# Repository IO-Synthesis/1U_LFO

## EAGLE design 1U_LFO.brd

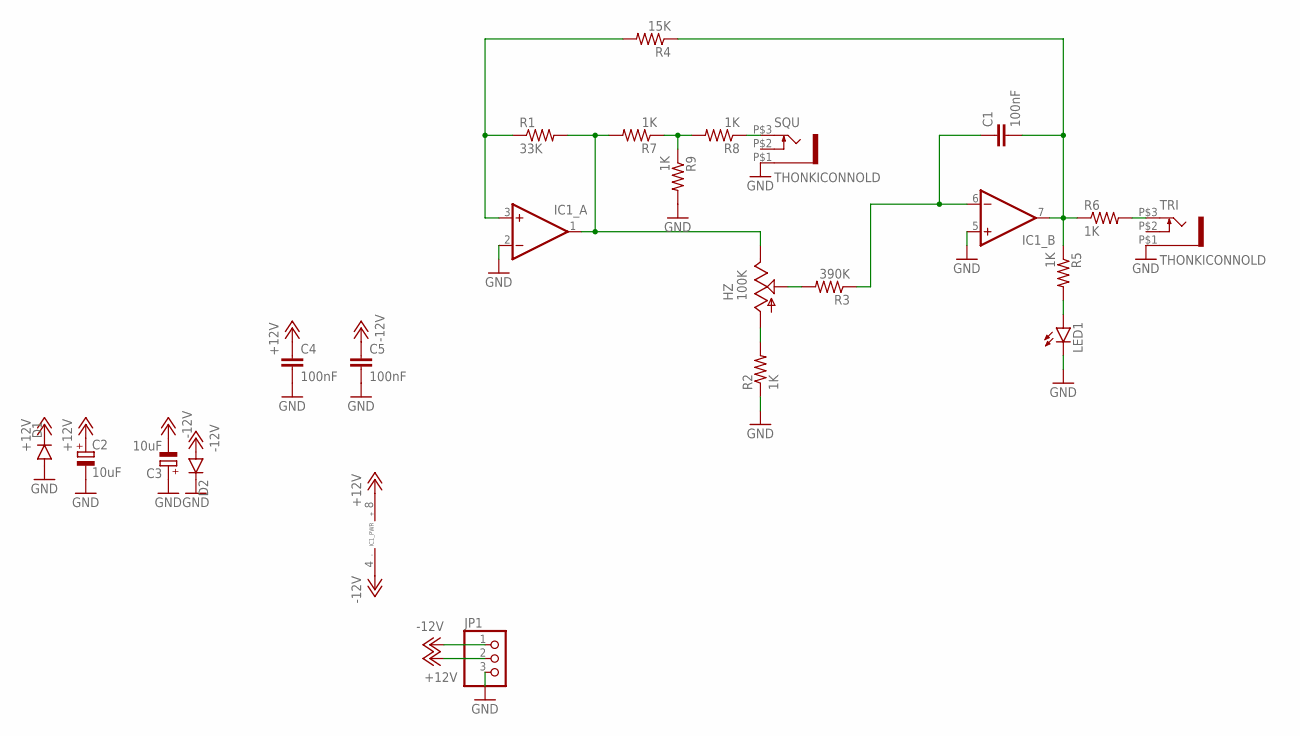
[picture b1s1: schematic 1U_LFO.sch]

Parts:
C1, C4, C5: 100nF; 0603-CAP
C2, C3: 10uF; CASE_B
D1, D2: DIODESOD123; SOD-123
HZ: 100K; 9MM_SNAP-IN_POT
IC1: DUALSMD; SO08
JP1: EUROPWR_TILE-TILE; 1X03_EUROPWR_TILE
LED1: LED3MM
R1: 33K; 0603-RES
R2, R5, R6, R7, R8, R9: 1K; 0603-RES
R3: 390K; 0603-RES
R4: 15K; 0603-RES
SQU: THONKICONNOLD; THONKICONN
TRI: THONKICONNOLD; THONKICONN

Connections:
+12V: C2.+, C4.1, D1.C, IC1.8 (V+), JP1.2
-12V: C3.-, C5.1, D2.A, IC1.4 (V-), JP1.1
GND: C2.-, C3.+, C4.2, C5.2, D1.A, D2.C, IC1.2 (-IN), IC1.5 (+IN), JP1.3, LED1.K (C), R2.1, R9.2, SQU.P$1 (5), TRI.P$1 (5)
unnamed: HZ.3 (E), IC1.1 (OUT), R1.2, R7.2
unnamed: HZ.1 (A), R2.2
unnamed: HZ.2 (S), R3.2
unnamed: C1.1, IC1.6 (-IN), R3.1
unnamed: IC1.3 (+IN), R1.1, R4.2
unnamed: C1.2, IC1.7 (OUT), R4.1, R5.1, R6.1
unnamed: LED1.A, R5.2
unnamed: R6.2, TRI.P$3 (3)
unnamed: R8.1, SQU.P$3 (3)
unnamed: R7.1, R8.2, R9.1

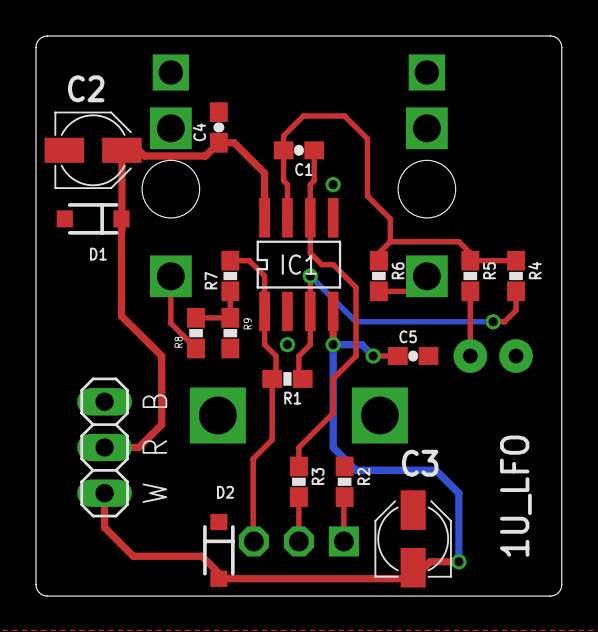
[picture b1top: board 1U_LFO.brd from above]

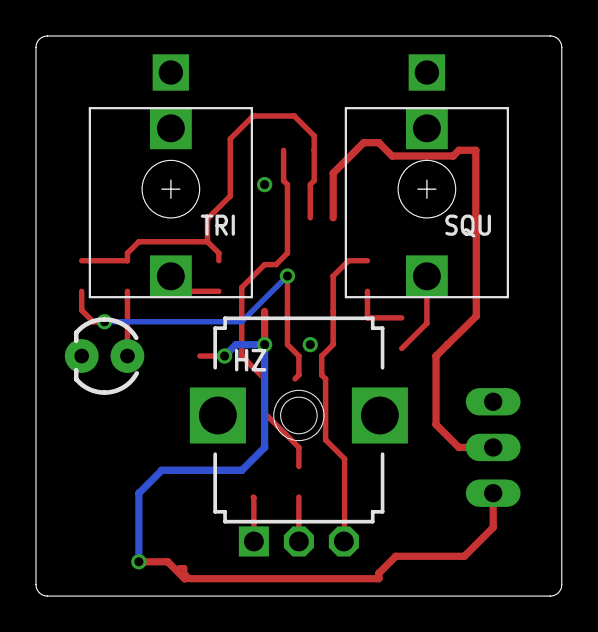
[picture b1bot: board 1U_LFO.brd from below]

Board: 2 copper layers, 29.2 x 31.1 mm, 22 parts (4 on the bottom side), 13 nets.

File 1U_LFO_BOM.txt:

Partlist exported from C:/Users/Erik/Documents/GitHub/1U_LFO/1U_LFO.sch at 4/30/2017 8:35 AM

Part Value         Device               Package           Description                                       
C1   100nF         CAP0603-CAP          0603-CAP          Capacitor                                         
C2   10uF          CAPACITOR_POL-CASE_B CASE_B            Polarized capacitor in various packages           
C3   10uF          CAPACITOR_POL-CASE_B CASE_B            Polarized capacitor in various packages           
C4   100nF         CAP0603-CAP          0603-CAP          Capacitor                                         
C5   100nF         CAP0603-CAP          0603-CAP          Capacitor                                         
D1                 DIODESOD123          SOD-123           Diode                                             
D2                 DIODESOD123          SOD-123           Diode                                             
HZ   100K          9MM_SNAP-IN_POT_     9MM_SNAP-IN_POT   9mm vertical snap-in pot, Alpha / Panasonic style 
IC1                DUALSMD              SO08              OP AMP                                            
JP1                EUROPWR_TILE-TILE    1X03_EUROPWR_TILE PIN HEADER                                        
LED1               LED3MM               LED3MM            LEDs                                              
R1   33K           RESISTOR0603-RES     0603-RES          Resistor                                          
R2   1K            RESISTOR0603-RES     0603-RES          Resistor                                          
R3   390K          RESISTOR0603-RES     0603-RES          Resistor                                          
R4   15K           RESISTOR0603-RES     0603-RES          Resistor                                          
R5   1K            RESISTOR0603-RES     0603-RES          Resistor                                          
R6   1K            RESISTOR0603-RES     0603-RES          Resistor                                          
R7   1K            RESISTOR0603-RES     0603-RES          Resistor                                          
R8   1K            RESISTOR0603-RES     0603-RES          Resistor                                          
R9   1K            RESISTOR0603-RES     0603-RES          Resistor                                          
SQU  THONKICONNOLD THONKICONNOLD        THONKICONN        3.5mm socket for Eurorack modular synths          
TRI  THONKICONNOLD THONKICONNOLD        THONKICONN        3.5mm socket for Eurorack modular synths

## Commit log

2017-01-09 :lollipop: Added .gitattributes & .gitignore files
2017-03-18 1U_LFO
2017-05-11 1U LFO
    Basic Low Frequency Oscillator

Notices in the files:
parts and their libraries:
SparkFun-LED: Licensing: Creative Commons ShareAlike 4.0 International - https://creativecommons.org/licenses/by-sa/4.0
